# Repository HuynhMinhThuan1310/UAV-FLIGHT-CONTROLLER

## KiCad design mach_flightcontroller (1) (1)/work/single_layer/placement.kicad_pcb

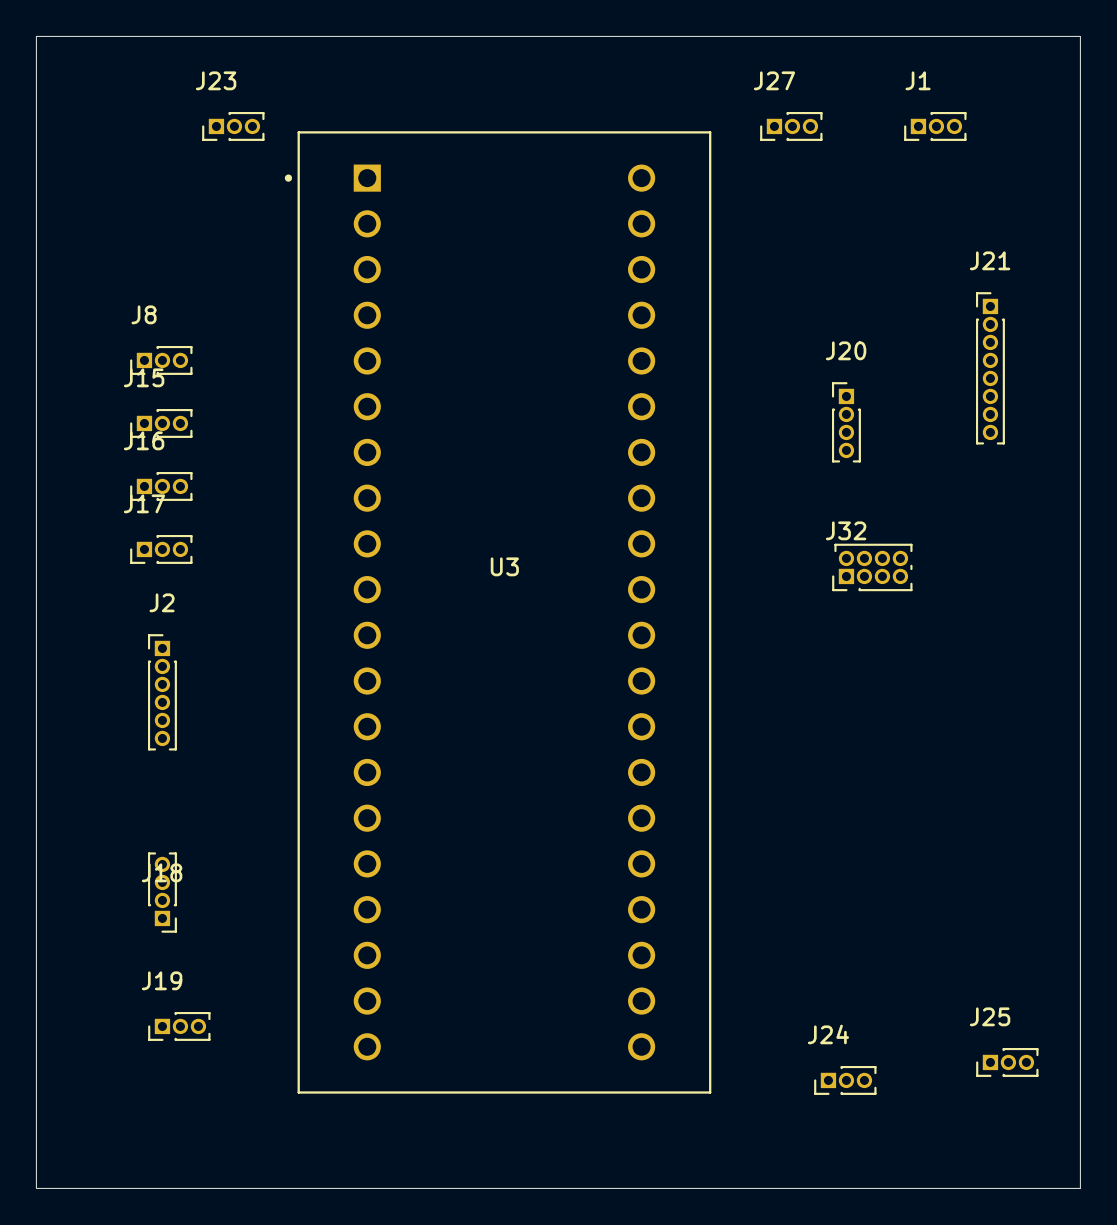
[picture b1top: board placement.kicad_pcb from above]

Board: 2 copper layers, 58.0 x 64.0 mm, 17 parts (1 on the bottom side), 27 nets, no tracks yet.

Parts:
J1: Receiver; PinHeader_1x03_P1.00mm_Vertical
J2: Receiver2; PinHeader_1x06_P1.00mm_Vertical
J8: ESC1; PinHeader_1x03_P1.00mm_Vertical
J15: ESC2; PinHeader_1x03_P1.00mm_Vertical
J16: ESC3; PinHeader_1x03_P1.00mm_Vertical
J17: ESC4; PinHeader_1x03_P1.00mm_Vertical
J18: UART3; PinHeader_1x04_P1.00mm_Vertical
J19: ADC0; PinHeader_1x03_P1.00mm_Vertical
J20: I2C; PinHeader_1x04_P1.00mm_Vertical
J21: IMU; PinHeader_1x08_P1.00mm_Vertical
J23: AUX_PWM; PinHeader_1x03_P1.00mm_Vertical
J24: GPIO1; PinHeader_1x03_P1.00mm_Vertical
J25: GPIO2; PinHeader_1x03_P1.00mm_Vertical
J26: GPS; JST_SH_BM06B-SRSS-TB_1x06-1MP_P1.00mm_Vertical
J27: SERVO; PinHeader_1x03_P1.00mm_Vertical
J32: NRF; PinHeader_2x04_P1.00mm_Vertical
U3: Bluepill_STM32; MODULE_ZC323000

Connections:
3.3: J18.4, J19.1, J20.4, J21.2, J23.2, J24.1, J25.1, J32.8, U3.18 (3.3), U3.40 (3.3)
/5V_BEC: J1.2, J17.2, J27.2, U3.38 (5V)
/5V_BEC1: J15.2, J26.4
/B13: J32.2, U3.22 (B13)
/B14: J32.5, U3.23 (B14)
/ESC1: J8.3, U3.5 (A0)
/ESC2: J15.3, U3.6 (A1)
/ESC3: J16.3, U3.7 (A2)
/ESC4: J17.3, U3.8 (A3)
/GPIO1: J24.3, U3.21 (B12)
/RECV-CH6: J2.6, U3.37 (B9)
/RECV_CH1: J2.1, U3.11 (A6)
/RECV_CH2: J2.2, U3.12 (A7)
/RECV_CH3: J2.3, U3.13 (B0)
/RECV_CH4: J2.4, U3.14 (B1)
/RECV_CH5: J2.5, U3.36 (B8)
/SCL: J20.2, J21.4, J26.5, U3.34 (B6)
/SDA: J20.1, J21.5, J26.6, U3.35 (B7)
/SPI1_CS: J32.7, U3.30 (A15)
/SPI1_MISO: J32.4, U3.32 (B4)
/SPI1_MOSI: J32.6, U3.33 (B5)
/SPI1_SCK: J32.3, U3.31 (B3)
/USART1_RX: J26.2, U3.27 (A10)
/USART1_TX: J26.1, U3.26 (A9)
/USART3_RX: J18.2, U3.16 (B11)
/USART3_TX: J18.3, U3.15 (B10)
G: J1.1, J8.1, J15.1, J16.1, J17.1, J18.1, J19.2, J20.3, J21.3, J23.1, J24.2, J25.2, J26.3, J27.1, J32.1, U3.19 (G), U3.20 (G), U3.39 (G)
